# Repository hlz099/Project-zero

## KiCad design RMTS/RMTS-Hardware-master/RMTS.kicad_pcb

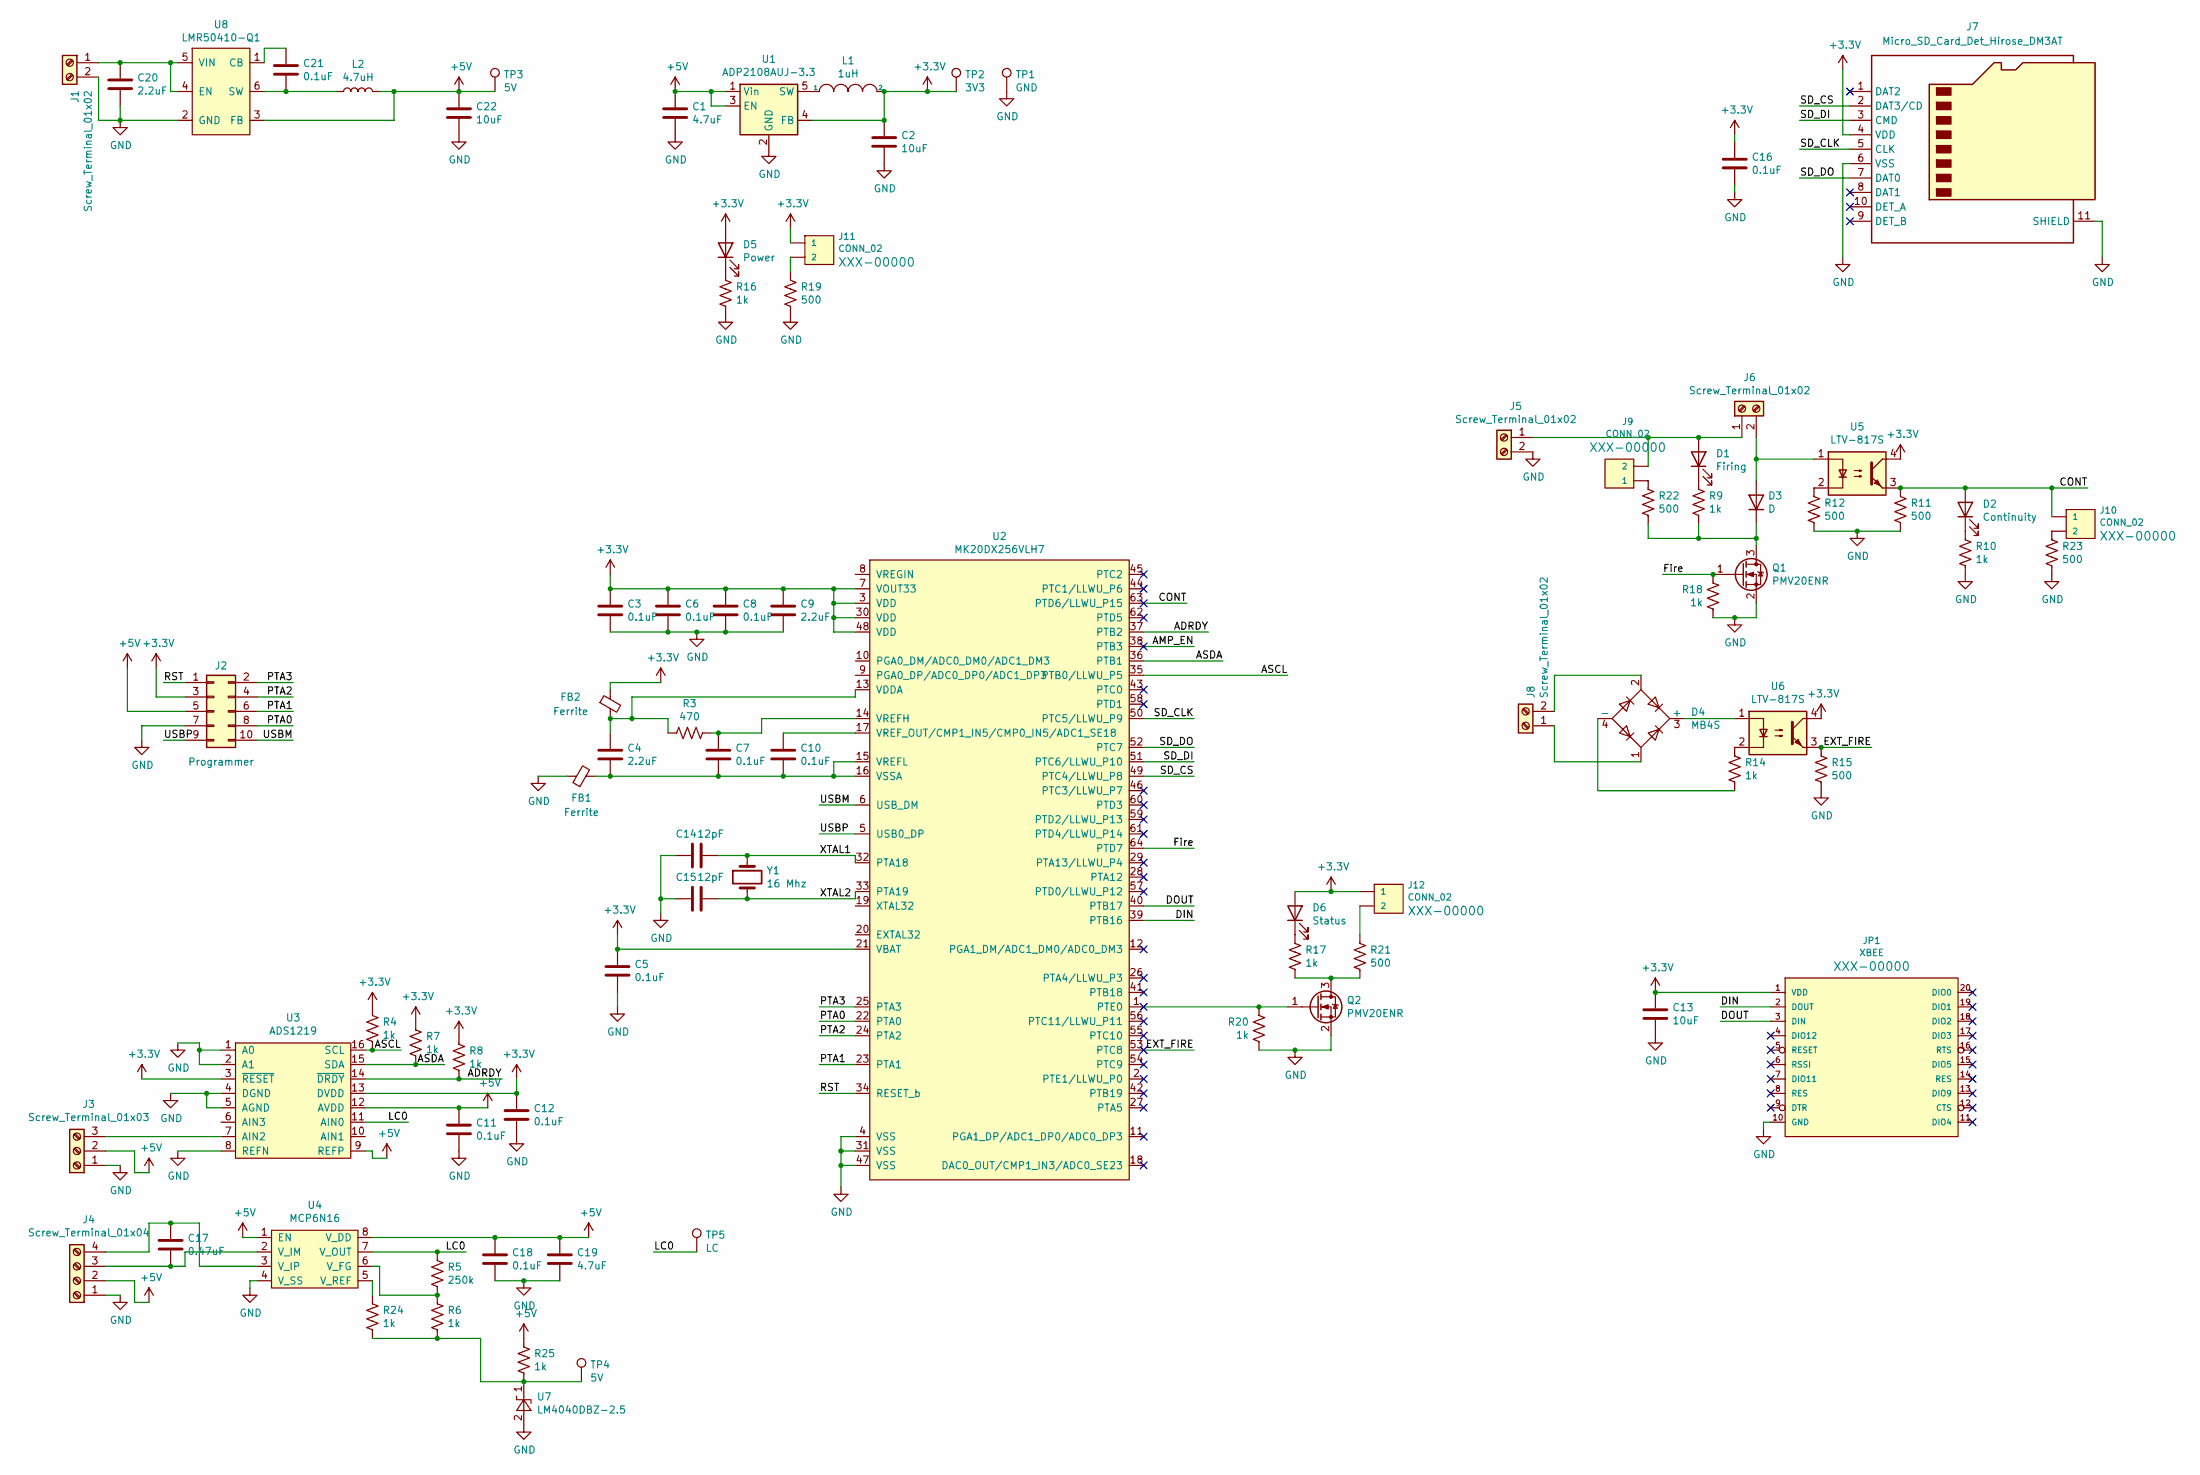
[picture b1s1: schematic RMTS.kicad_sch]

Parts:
C1, C19: 4.7uF; C_0805_2012Metric_Pad1.15x1.40mm_HandSolder; LCSC C1779
C2: 10uF; CP_Elec_5x3.9
C3, C5, C6, C7, C8, C10, C11, C12, C16, C18, C21: 0.1uF; C_0805_2012Metric_Pad1.15x1.40mm_HandSolder; LCSC C49678
C4, C9, C20: 2.2uF; C_0805_2012Metric_Pad1.15x1.40mm_HandSolder; LCSC C49217
C13, C22: 10uF; C_0805_2012Metric_Pad1.15x1.40mm_HandSolder; LCSC C15850
C14, C15: 12pF; C_0805_2012Metric_Pad1.15x1.40mm_HandSolder; LCSC C1792
C17: 0.47uF; C_0805_2012Metric_Pad1.15x1.40mm_HandSolder; LCSC C13967
D1: Firing; LED_0805_2012Metric_Pad1.15x1.40mm_HandSolder; LCSC C84256
D2: Continuity; LED_0805_2012Metric_Pad1.15x1.40mm_HandSolder; LCSC C84256
D3: D; D_SOD-128
D4: MB4S; TO-269AA; LCSC C151727
D5: Power; LED_0805_2012Metric_Pad1.15x1.40mm_HandSolder; LCSC C84256
D6: Status; LED_0805_2012Metric_Pad1.15x1.40mm_HandSolder; LCSC C84256
FB1, FB2: Ferrite; C_0805_2012Metric_Pad1.15x1.40mm_HandSolder; LCSC C97001
J1, J5, J6, J8: Screw_Terminal_01x02; SCREWTERMINAL-3.5MM-2
J2: Programmer; PinHeader_2x05_P2.00mm_Vertical
J3: Screw_Terminal_01x03; SCREWTERMINAL-3.5MM-3
J4: Screw_Terminal_01x04; SCREWTERMINAL-3.5MM-4
J7: Micro_SD_Card_Det_Hirose_DM3AT; microSD_HC_Hirose_DM3AT-SF-PEJM5
J9, J10, J11, J12: CONN_02; 1X02
JP1: XBEE
L1: 1uH; L_0805_2012Metric_Pad1.15x1.40mm_HandSolder; LCSC C1042
L2: 4.7uH; L_0805_2012Metric_Pad1.15x1.40mm_HandSolder; LCSC C86090
Q1, Q2: PMV20ENR; SOT-23; LCSC C456088
R3: 470; R_0805_2012Metric_Pad1.15x1.40mm_HandSolder; LCSC C17710
R4, R6, R7, R8, R9, R10, R14, R16, R17, R18, R20, R24, R25: 1k; R_0805_2012Metric_Pad1.15x1.40mm_HandSolder; LCSC C17513
R5: 250k; R_0805_2012Metric_Pad1.15x1.40mm_HandSolder; LCSC C25825
R11, R12, R15, R19, R22, R23: 500; R_0805_2012Metric_Pad1.15x1.40mm_HandSolder; LCSC C17734
R21: 500; R_0805_2012Metric_Pad1.15x1.40mm_HandSolder; LCSC C17513
TP1: GND; TestPoint_THTPad_2.0x2.0mm_Drill1.0mm
TP2: 3V3; TestPoint_THTPad_2.0x2.0mm_Drill1.0mm
TP3, TP4: 5V; TestPoint_THTPad_2.0x2.0mm_Drill1.0mm
TP5: LC; TestPoint_THTPad_2.0x2.0mm_Drill1.0mm
U1: ADP2108AUJ-3.3; TSOT-23-5; LCSC C143875
U2: MK20DX256VLH7; LQFP-64_10x10mm_P0.5mm
U3: ADS1219; TSSOP-16_4.4x5mm_P0.65mm
U4: MCP6N16; MSOP-8_3x3mm_P0.65mm
U5, U6: LTV-817S; SMDIP-4_W9.53mm; LCSC C22113
U7: LM4040DBZ-2.5; SOT-23
U8: LMR50410-Q1; SOT-23-6
Y1: 16 Mhz; Crystal_HC49-U_Vertical

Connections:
+3V3: C2.1, C3.1, C5.1, C6.1, C8.1, C9.1, C12.1, C13.1, C16.1, D5.2 (A), D6.2 (A), FB2.1, J2.3, J7.4 (VDD), J11.1, J12.1, JP1.1 (VDD), L1.2, R4.1, R7.1, R8.1, TP2.1, U1.4 (FB), U2.3 (VDD), U2.7 (VOUT33), U2.21 (VBAT), U2.30 (VDD), U2.48 (VDD), U3.3 (~RESET), U3.13 (DVDD), U5.4, U6.4
+5V: C1.1, C11.1, C18.1, C19.1, C22.1, J2.5, J3.2, J4.2, L2.2, R25.1, TP3.1, U1.1 (Vin), U1.3 (EN), U3.9 (REFP), U3.12 (AVDD), U4.1 (EN), U4.8 (V_DD), U8.3 (FB)
/ADRDY: R8.2, U2.37 (PTB2), U3.14 (~DRDY)
/AMP_EN: U2.38 (PTB3)
/ASCL: R4.2, U2.35 (PTB0/LLWU_P5), U3.16 (SCL)
/ASDA: R7.2, U2.36 (PTB1), U3.15 (SDA)
/CONT: D2.2 (A), J10.1, R11.1, U2.63 (PTD6/LLWU_P15), U5.3
/DIN: JP1.2 (DOUT), U2.39 (PTB16)
/DOUT: JP1.3 (DIN), U2.40 (PTB17)
/EXT_FIRE: R15.1, U2.53 (PTC8), U6.3
/Fire: Q1.1 (G), R18.1, U2.64 (PTD7)
/LC0: R5.1, TP5.1, U3.11 (AIN0), U4.7 (V_OUT)
/PTA0: J2.8, U2.22 (PTA0)
/PTA1: J2.6, U2.23 (PTA1)
/PTA2: J2.4, U2.24 (PTA2)
/PTA3: J2.2, U2.25 (PTA3)
/RST: J2.1, U2.34 (RESET_b)
/SD_CLK: J7.5 (CLK), U2.50 (PTC5/LLWU_P9)
/SD_CS: J7.2 (DAT3/CD), U2.49 (PTC4/LLWU_P8)
/SD_DI: J7.3 (CMD), U2.51 (PTC6/LLWU_P10)
/SD_DO: J7.7 (DAT0), U2.52 (PTC7)
/USBM: J2.10, U2.6 (USB_DM)
/USBP: J2.9, U2.5 (USB0_DP)
/XTAL1: C14.1, U2.32 (PTA18), Y1.1
/XTAL2: C15.1, U2.33 (PTA19), Y1.2
GND: C1.2, C2.2, C3.2, C5.2, C6.2, C8.2, C9.2, C11.2, C12.2, C13.2, C14.2, C15.2, C16.2, C18.2, C19.2, C20.2, C22.2, FB1.1, J1.2, J2.7, J3.1, J4.1, J5.2, J7.6 (VSS), J7.11 (SHIELD), JP1.10 (GND), Q1.2 (S), Q2.2 (S), R10.2, R11.2, R12.2, R15.2, R16.2, R18.2, R19.2, R20.2, R23.2, TP1.1, U1.2 (GND), U2.4 (VSS), U2.31 (VSS), U2.47 (VSS), U3.1 (A0), U3.2 (A1), U3.4 (DGND), U3.5 (AGND), U3.8 (REFN), U4.4 (V_SS), U7.2 (A), U8.2 (GND)
unnamed: D1.1 (K), R9.1
unnamed: D2.1 (K), R10.1
unnamed: D3.2 (A), J6.2, U5.1
unnamed: D3.1 (K), Q1.3 (D), R9.2, R22.2
unnamed: D4.3 (+), U6.1
unnamed: D4.4 (-), R14.2
unnamed: D5.1 (K), R16.1
unnamed: D6.1 (K), R17.1
unnamed: C20.1, J1.1, U8.4 (EN), U8.5 (VIN)
unnamed: J3.3, U3.7 (AIN2)
unnamed: C17.2, J4.3, U4.2 (V_IM)
unnamed: C17.1, J4.4, U4.3 (V_IP)
unnamed: D4.1, J8.1
unnamed: D4.2, J8.2
unnamed: J9.1, R22.1
unnamed: J10.2, R23.1
unnamed: J11.2, R19.1
unnamed: J12.2, R21.1
unnamed: Q2.3 (D), R17.2, R21.2
unnamed: R12.1, U5.2
unnamed: R14.1, U6.2
unnamed: L1.1, U1.5 (SW)
unnamed: C4.1, FB2.2, R3.2, U2.13 (VDDA)
unnamed: C7.1, R3.1, U2.14 (VREFH)
unnamed: C4.2, C7.2, C10.2, FB1.2, U2.15 (VREFL), U2.16 (VSSA)
unnamed: C10.1, U2.17 (VREF_OUT/CMP1_IN5/CMP0_IN5/ADC1_SE18)
unnamed: R5.2, R6.1, U4.6 (V_FG)
unnamed: R24.1, U4.5 (V_REF)
unnamed: R6.2, R24.2, R25.2, TP4.1, U7.1 (K)
unnamed: C21.1, U8.1 (CB)
unnamed: C21.2, L2.1, U8.6 (SW)

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
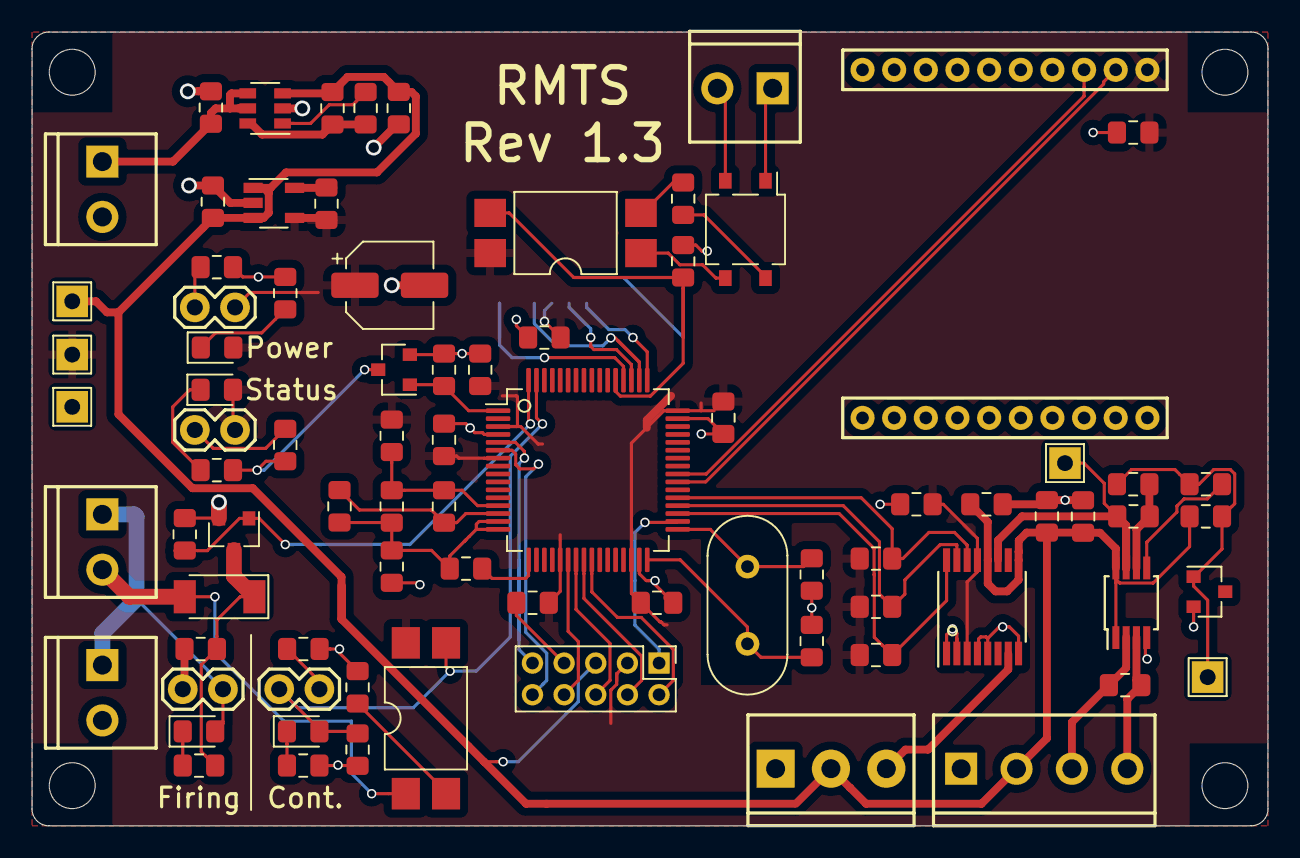
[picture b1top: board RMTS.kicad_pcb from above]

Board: 2 copper layers, 78.1 x 50.2 mm, 83 parts (1 on the bottom side), 57 nets.

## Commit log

2024-10-23 upload AeroLab
2024-10-23 upload AVL
2024-10-23 upoad CD-nozzle
2024-10-23 upload Filament-winding-1
2024-10-23 upload Filament-winding-2
2024-10-23 upload Filament-winding-3
2024-10-23 upload Filament-winding-4
2024-10-23 upload Filament-winding-5
2024-10-23 upload Filament-winding-6
2024-10-23 upload Filament-winding-7
2024-10-23 upload Filament-winding-8
2024-10-23 upload Filament-winding-9
2024-10-23 upload Filament-winding-10
2024-10-23 upload Filament-winding-11
2024-10-23 upload Filament-winding-12
2024-10-23 upload Filament-winding-13
2024-10-23 upload Filament-winding-14
2024-10-23 upload Filament-winding-15
2024-10-23 Terminal20141030-Strand Burner
2024-10-23 upload xfoil
2024-10-23 upload winplot
2024-10-23 upload tctracer
2024-10-23 upload ProPEP
2024-10-23 upload RMTS
2024-10-23 upload NASAUCPJavaStandalone-master
2024-10-23 upload OpenMotor-staging
2024-10-23 updload Propulsion-master
2024-10-23 upload TL
2024-10-23 upload EMTG
2024-10-23 upload TLNS3D
2024-10-24 upload CEA
2024-11-07 upload Applied-Deep-Learning-with-Keras
2024-11-07 update Applied-Deep-Learning-with-Keras
2024-11-29 upload FBP
2025-01-08 upload RPA-C
2025-01-08 upload CFL-3D
2025-01-08 upload CFL3D
